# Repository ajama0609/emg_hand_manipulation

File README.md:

# EMG Hand Gesture Classification

## Introduction

Surface electromyography (sEMG) is a non-invasive technique for measuring muscle electrical activity and is widely used in human–machine interfaces, prosthetics, and rehabilitation systems. Reliable sEMG systems require low-noise analog front-ends, high common-mode rejection, stable power delivery, and careful PCB layout to preserve signal integrity, particularly given the low-amplitude (µV–mV) nature of EMG signals.

This project details the design, fabrication, and validation of a custom surface electromyography (sEMG) acquisition board intended to capture high-fidelity muscle signals for both real-time and offline analysis. Bypassing commercial development kits, a fully custom printed circuit board (PCB) was developed to directly address the practical engineering challenges inherent in analog signal conditioning, proper grounding techniques, filtering, and the integration of mixed-signal systems ---

# Hardware Development and Testing
A custom sEMG acquisition hardware board has been designed and fabricated to enable lightweight, low-latency, and high-fidelity signal capture for real-time applications.

### Key Components and BOM Highlights:

- **Instrumentation Amplifiers:** Texas Instruments INA333 (3 units) for high CMRR and low noise EMG signal amplification  
- **Microcontroller:** STM32F103C8T6 (ARM Cortex-M3) for signal processing and data acquisition  
- **Power Management:** Microchip MIC5504-3.3 LDO regulator for stable 3.3V supply  
- **ESD Protection:** STMicroelectronics USBLC6-2SC6 for USB interface protection  
- **Passive Components:** High-quality capacitors (e.g., TDK X5R, KEMET), resistors (Susumu, Yageo), and ferrite bead (Murata) for noise filtering and stable operation  
- **Connectors:** USB-C receptacle, 3.5mm audio jacks for signal output and power input  
- **Oscillator:** EPSON 16MHz crystal for clock generation

---

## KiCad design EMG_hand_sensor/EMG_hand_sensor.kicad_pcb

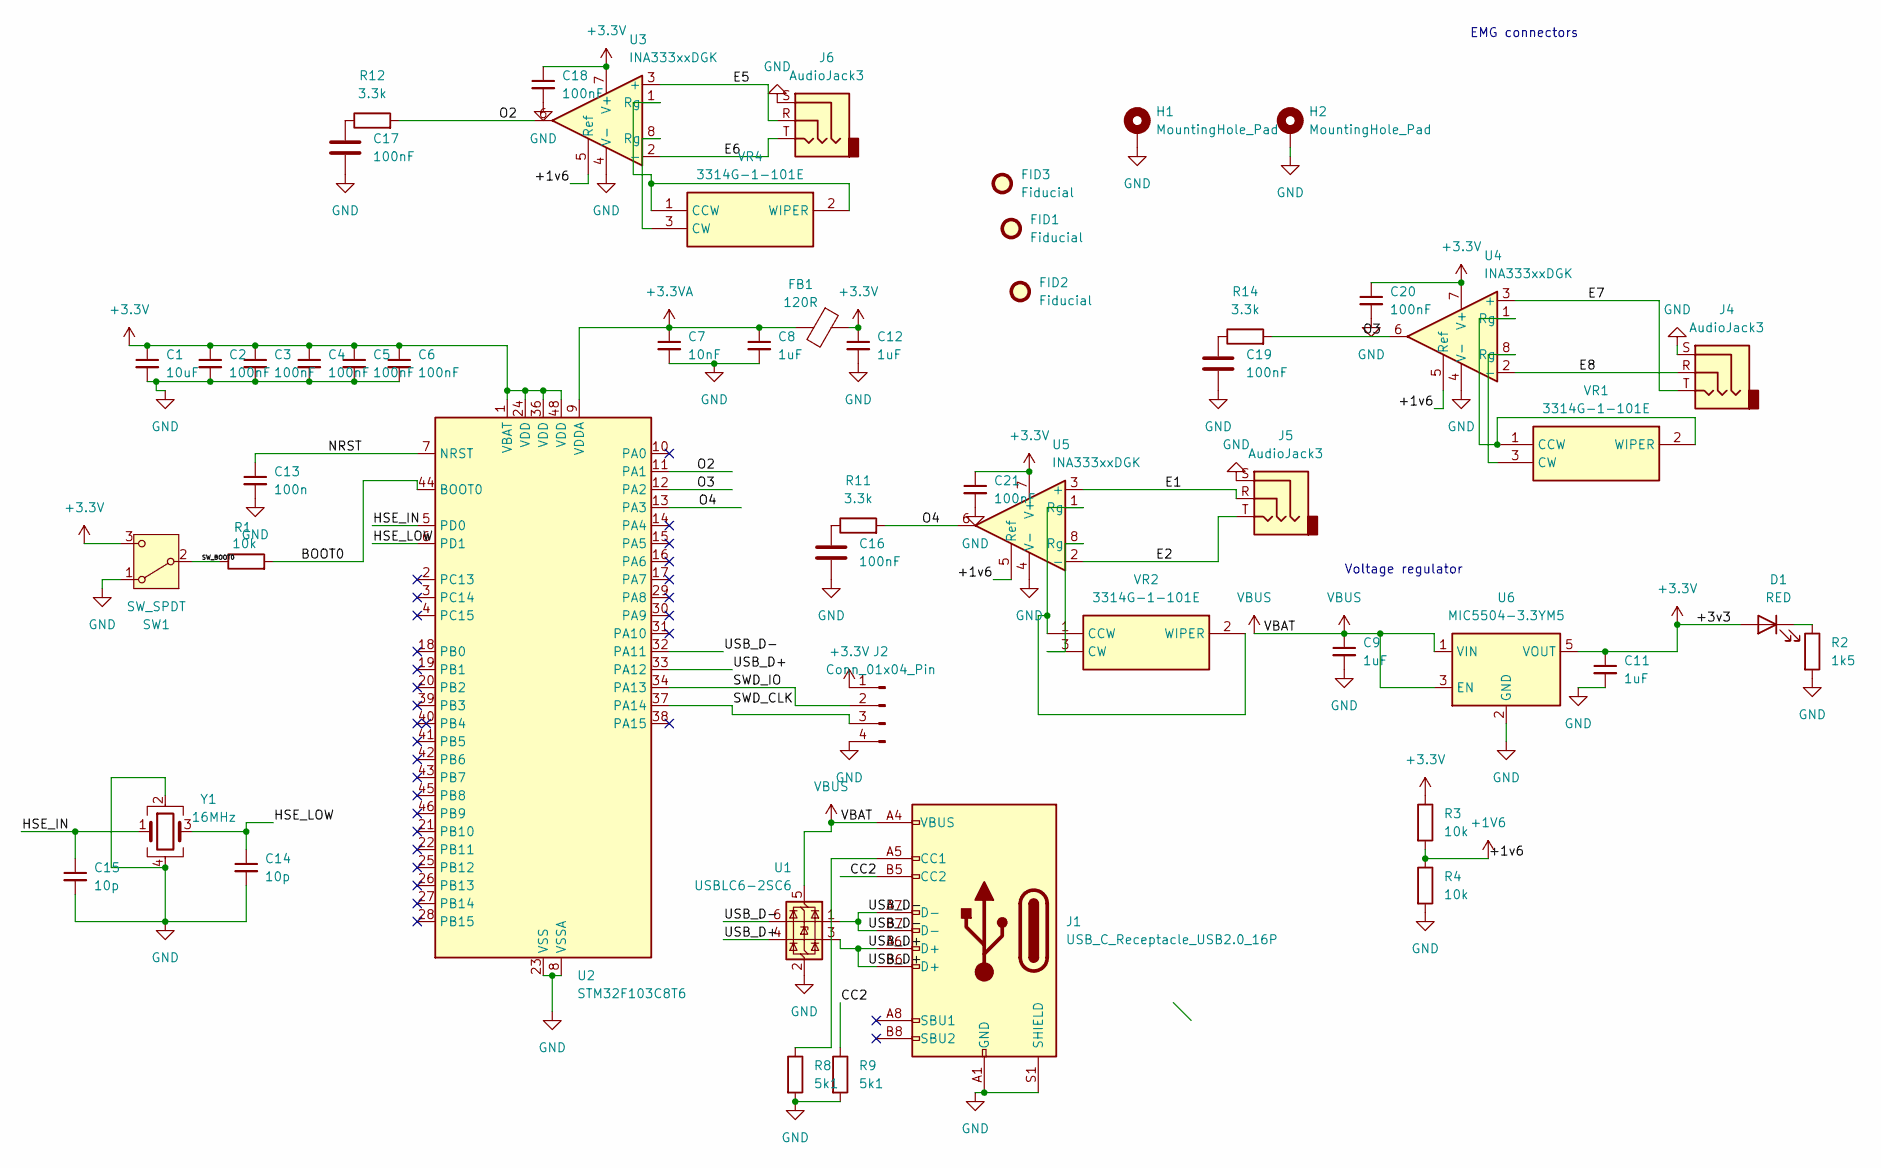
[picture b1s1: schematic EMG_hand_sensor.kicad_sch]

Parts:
C1: 10uF; C_0805_2012Metric_Pad1.18x1.45mm_HandSolder
C2, C3, C4, C5, C6, C16, C17, C18, C19, C20, C21: 100nF; C_0805_2012Metric_Pad1.18x1.45mm_HandSolder
C7: 10nF; C_0805_2012Metric_Pad1.18x1.45mm_HandSolder
C8, C9, C11, C12: 1uF; C_0805_2012Metric_Pad1.18x1.45mm_HandSolder
C13: 100n; C_0805_2012Metric_Pad1.18x1.45mm_HandSolder
C14, C15: 10p; C_0805_2012Metric_Pad1.18x1.45mm_HandSolder
D1: RED; D_0805_2012Metric
FB1: 120R; BLM21AG102BH1J
FID1, FID2, FID3: Fiducial; Fiducial_0.5mm_Mask2mm
H1, H2: MountingHole_Pad; MountingHole_2.2mm_M2_Pad
J1: USB_C_Receptacle_USB2.0_16P; USB_C_Receptacle_GCT_USB4105-xx-A_16P_TopMnt_Horizontal
J2: Conn_01x04_Pin; PinHeader_1x04_P2.54mm_Vertical
J4, J5, J6: AudioJack3; Jack_3.5mm_CUI_SJ-3523-SMT_Horizontal
R1, R3, R4: 10k; R_0805_2012Metric_Pad1.20x1.40mm_HandSolder
R2: 1k5; R_0805_2012Metric_Pad1.20x1.40mm_HandSolder
R8, R9: 5k1; R_0805_2012Metric_Pad1.20x1.40mm_HandSolder
R11, R12, R14: 3.3k; R_0805_2012Metric_Pad1.20x1.40mm_HandSolder
SW1: SW_SPDT; SW_SPDT_CK_JS102011SAQN
U1: USBLC6-2SC6; SOT-23-6
U2: STM32F103C8T6; LQFP-48_7x7mm_P0.5mm
U3, U4, U5: INA333xxDGK; VSSOP-8_3x3mm_P0.65mm
U6: MIC5504-3.3YM5; SOT-23-5
VR1, VR2, VR4: 3314G-1-101E; 3314G-1; Mouser Part Number 652-3314G-1-101E
Y1: 16MHz; Crystal_SMD_3225-4Pin_3.2x2.5mm

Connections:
+1V6: R3.2, R4.1, U3.5 (Ref), U4.5 (Ref), U5.5 (Ref)
+3.3V: C1.1, C2.1, C3.1, C4.1, C5.1, C6.1, C11.1, C12.1, C18.1, C20.1, C21.1, D1.2 (A), FB1.1, J2.1, R3.1, SW1.3 (C), U2.1 (VBAT), U2.24 (VDD), U2.36 (VDD), U2.48 (VDD), U3.7 (V+), U4.7 (V+), U5.7 (V+), U6.5 (VOUT)
+3.3VA: C7.1, C8.1, FB1.2, U2.9 (VDDA)
/BOOT0: R1.2, U2.44 (BOOT0)
/CC2: J1.B5 (CC2), R9.1
/E1: J5.R, U5.3 (+)
/E2: J5.T, U5.2 (-)
/E5: J6.R, U3.3 (+)
/E6: J6.T, U3.2 (-)
/E7: J4.T, U4.3 (+)
/E8: J4.R, U4.2 (-)
/HSE_IN: C15.1, U2.5 (PD0), Y1.1
/HSE_LOW: C14.1, U2.6 (PD1), Y1.3
/NRST: C13.1, U2.7 (NRST)
/O2: R12.2, U2.11 (PA1), U3.6
/O3: R14.2, U2.12 (PA2), U4.6
/O4: R11.2, U2.13 (PA3), U5.6
/SWD_CLK: J2.3, U2.37 (PA14)
/SWD_IO: J2.2, U2.34 (PA13)
/SW_BOOT0: R1.1, SW1.2 (B)
/USB_D+: J1.A6 (D+), J1.B6 (D+), U1.3 (I/O2), U1.4 (I/O2), U2.33 (PA12)
/USB_D-: J1.A7 (D-), J1.B7 (D-), U1.1 (I/O1), U1.6 (I/O1), U2.32 (PA11)
GND: C1.2, C2.2, C3.2, C4.2, C5.2, C6.2, C7.2, C8.2, C9.2, C11.2, C12.2, C13.2, C14.2, C15.2, C16.2, C17.2, C18.2, C19.2, C20.2, C21.2, H1.1, H2.1, J1.A1 (GND), J1.A12 (GND), J1.B1 (GND), J1.B12 (GND), J1.S1 (SHIELD), J2.4, J4.S, J5.S, J6.S, R2.2, R4.2, R8.2, R9.2, SW1.1 (A), U1.2 (GND), U2.8 (VSSA), U2.23 (VSS), U2.35 (VSS), U2.47 (VSS), U3.4 (V-), U4.4 (V-), U5.4 (V-), U6.2 (GND), Y1.2, Y1.4
unnamed: C16.1, R11.1
unnamed: C17.1, R12.1
unnamed: C19.1, R14.1
unnamed: D1.1 (K), R2.1
unnamed: J1.A5 (CC1), R8.1
unnamed: U4.1 (Rg), VR1.1 (CCW), VR1.2 (WIPER)
unnamed: U4.8 (Rg), VR1.3 (CW)
unnamed: U5.1 (Rg), VR2.1 (CCW), VR2.2 (WIPER)
unnamed: U5.8 (Rg), VR2.3 (CW)
unnamed: U3.1 (Rg), VR4.1 (CCW), VR4.2 (WIPER)
unnamed: U3.8 (Rg), VR4.3 (CW)
VBUS: C9.1, J1.A4 (VBUS), J1.A9 (VBUS), J1.B4 (VBUS), J1.B9 (VBUS), U1.5 (VBUS), U6.1 (VIN), U6.3 (EN)

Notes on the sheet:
Voltage regulator
EMG connectors

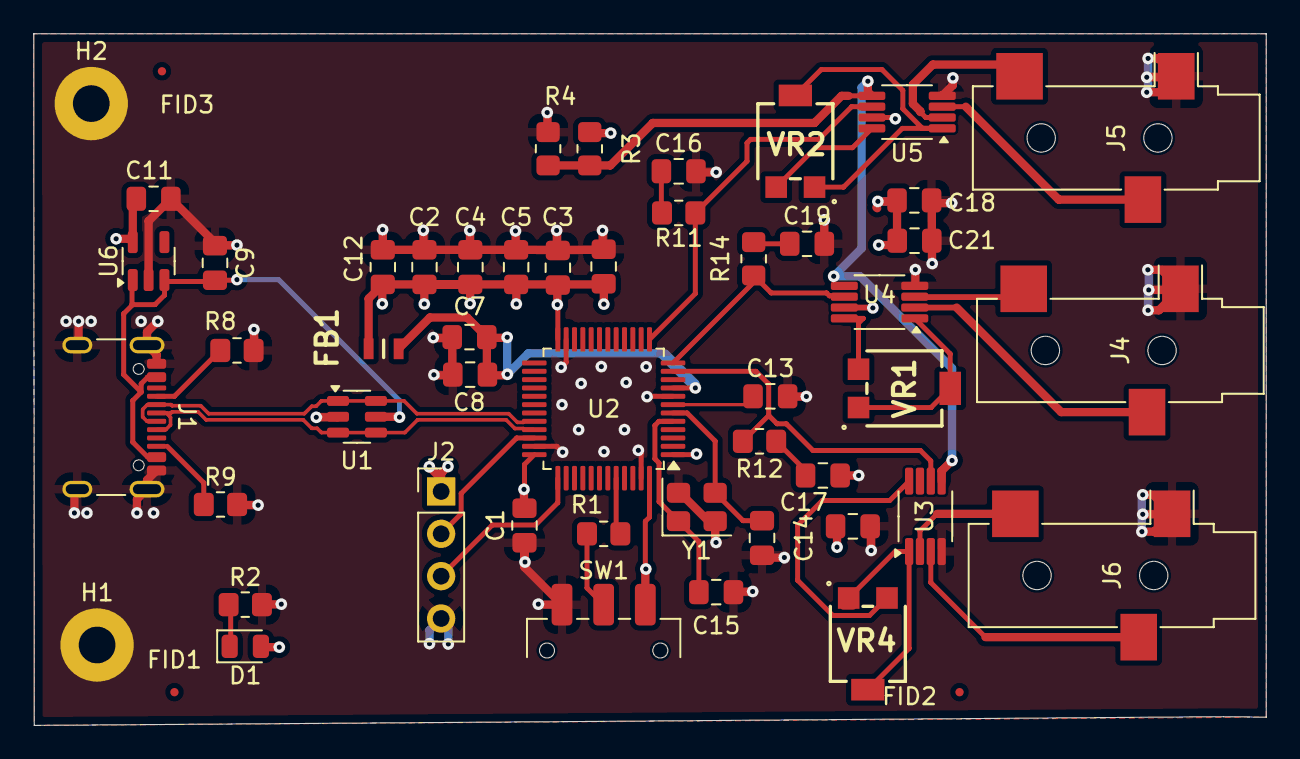
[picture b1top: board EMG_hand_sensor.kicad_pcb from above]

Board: 4 copper layers, 73.9 x 41.5 mm, 52 parts (0 on the bottom side), 35 nets.

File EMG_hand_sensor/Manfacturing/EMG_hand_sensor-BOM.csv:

"Designator","Quantity","Manufacturer","Manufacturer Part Number","Description","Package","Value","Type","Global Sourcing"
"C1","1","TDK","C2012X5R1E106M125AB","10uF Cap","0805","10uF","Capacitor",""
"C2,C3,C4,C5,C6,C16,C17,C18,C19,C20,C21","11","Vishay / Vitramon","GA0805Y104KBBBT31G","100nF Cap","0805","100nF","Capacitor",""
"C7","1","KEMET","C0805X103JCRAC3316","10nF Cap","0805","10nF","Capacitor",""
"C8,C9,C11,C12","4","KEMET","C0805X105J5RACAUTO","1uF Cap","0805","1uF","Capacitor",""
"C13","1","Vishay / Vitramon","GA0805Y104KBBBT31G","100nF Cap","0805","100n","Capacitor",""
"C14,C15","2","KEMET","C0805C100KDTACTU","10pF Cap","0805","10p","Capacitor",""
"D1","1","Kingbright","APT2012SURCK","Red LED","0805","RED","Diode",""
"FB1","1","Murata Electronics","BLM21AG102SN1D","Ferrite Bead","0805","120R","Ferrite",""
"J1","1","GCT","USB4105-GF-A","USB-C Receptacle","USB_C_16P","USB_C","Connector","Yes"
"J2","1","Würth Elektronik","61300411121","Pin Header 1x4","2.54mm","PinHeader","Connector","Yes"
"J4,J5,J6","3","CUI Devices","SJ-3523-SMT-TR","3.5mm Audio Jack","SJ-3523","AudioJack3","Connector","Yes"
"R1,R3,R4","3","Susumu","RR1220P-103-D","10k Resistor","0805","10k","Resistor",""
"R2","1","YAGEO","RC0805JR-071K5L","1.5k Resistor","0805","1k5","Resistor",""
"R8,R9","2","YAGEO","RC0402JR-074K7L","5.1k Resistor","0402","5k1","Resistor",""
"R11,R12,R14","3","Susumu","RG2012L-332-L-T05","3.3k Resistor","0805","3.3k","Resistor",""
"SW1","1","C&K","JS102011SAQN","SPDT Switch","SMD","SW_SPDT","Switch",""
"U1","1","STMicroelectronics","USBLC6-2SC6","USB ESD Suppressor","SOT-23-6","USBLC6-2SC6","IC",""
"U2","1","STMicroelectronics","STM32F103C8T6","STM32 MCU","LQFP-48","STM32F103C8T6","IC",""
"U3,U4,U5","3","Texas Instruments","INA333AIDGKR","Instrumentation Amplifier","VSSOP-8","INA333","IC","Yes"
"U6","1","Microchip Technology","MIC5504-3.3YM5-TR","LDO Regulator","SOT-23-5","3.3V","IC",""
"VR1,VR2,VR3","3","Vishay / Sfernice","TS53YJ501MR10","Potentiometer 500Ω","TH","500Ω","Potentiometer","Yes"
"Y1","1","EPSON","TSX-3225 16.0000MF10U-B0","16MHz Crystal","3225","16MHz","Crystal",""

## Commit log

2025-06-25 more commits
2025-06-25 viewing raw signals
2025-06-25 emg filtering
2025-06-26 FFT of the first window of the data
2025-06-26 filtered fft of first window
2025-06-26 RMS features of the raw EMG
2025-06-27 Smoothed RMS-good for envelope detection
2025-06-27 updated figures
2025-06-28 Classification script
2025-06-30 LTspice circuit for analogue frontend
2025-07-02 IIR_coeffs_for_board
2025-07-02 Extracted features as csv file next step parse it in python normalize it and use it as a input to my pytorch model
2025-07-02 EMG model
2025-07-02 updated python
2025-07-02 updated features
2025-07-02 Linear model training
2025-07-02 update emg_model
2025-07-02 renamed
2025-07-02 Unbalanced labels bug
2025-07-03 updated files
2025-07-03 model works now time to optimize!
2025-07-03 First training
2025-07-03 some more training
2025-07-04 Trying with 8 channels now
2025-07-04 Training going smoothly time to optimize model
2025-07-04 updated model
2025-07-04 image
2025-07-04 push
2025-07-04 new features
2025-07-04 stm32 files
2025-07-05 trying to not filter out the rest hand state
2025-07-05 model ~90% acc
2025-07-05 tidying up codebase
2025-07-07 building some more
2025-07-07 some changes
2025-07-07 Update:got both the hpf and lpf filter reponses
2025-07-07 added lstm model
2025-07-07 filters
2025-07-07 cleaning
2025-07-07 working lpf and hpf gains a bit funny on the hpf
2025-07-09 finished schematics and test
2025-07-09 finishing schmeatics
2025-07-10 finished with first schematic for now
2025-07-10 starting pcb design
2025-07-10 component placement and design rules
2025-07-10 completley chnaged from analog to digital
2025-07-10 running ERC
2025-07-10 new schematic done
2025-07-10 pcb design started layout
2025-07-10 starting pch layout
2025-07-11 design rules
2025-07-11 pcb layout finished
2025-07-11 routing time
2025-07-11 Need to add guard traces and vias and then I can start routing
2025-07-12 done with most of the routing
2025-07-12 Finalising board running DRC
2025-07-12 done DRC final checks
2025-07-12 ready for ordering
2025-07-12 gerber files and BOM
2025-07-12 order pending
2025-07-12 need to change some things because jlcpcb stock
2025-07-12 looks good
2025-07-13 done ordered
2025-07-13 some changes to imporve noise
2025-07-14 updated for cheaper parts
2025-07-14 ordered boards from jlcpcb
2025-07-16 snn features
2025-07-16 snn featues 34 columsn
2025-07-17 trying to incorporate snn
2025-07-17 snn 73% accuracy 0.19 MB model size
2025-07-17 70% on a 50kB model
2025-07-17 77% 50kB model
2025-07-17 model size
2025-07-17 76.9% acc 50kB model size
2025-07-19 ninaprodb1
2025-07-19 DB1 labelled feature extracted RMS
2025-07-19 SpikeEMG NinaproDB1
2025-07-19 got a functional script
2025-07-19 added frequency feats as well as time domain
2025-07-19 57% acc small SNN model TD features RMS,MAV,VAR
2025-07-19 restructured
2025-07-19 updated model script
2025-07-19 optimizing model
2025-07-19 tweaks
2025-07-19 getting closer to edge
2025-07-19 slighly larger
2025-07-20 4MB model 1ms inference 90%
2025-07-20 a bit sus
2025-07-20 not sure what to make of this
2025-07-20 Final model design for now
2025-07-20 writing README
2025-07-20 more changes
2025-07-23 cleaning up
2025-07-24 stacking feats
2025-07-24 very promising 95% acc
2025-07-25 benchmark against CNN
